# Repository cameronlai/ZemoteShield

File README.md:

# ZemoteShield
Zemote Shield for Zemote Universal Remote Control (on Arduino Uno and Nano)

This project, and all of its design files (including the layout), is licensed under the Creative Commons Attribution-ShareAlike 3.0 Unported license.

Related pages
- Project page: http://cameronlai.com/zemote/
- Zemote Firmware: https://github.com/cameronlai/ZemoteFirmware
- Zemote Host: https://github.com/cameronlai/ZemoteHost

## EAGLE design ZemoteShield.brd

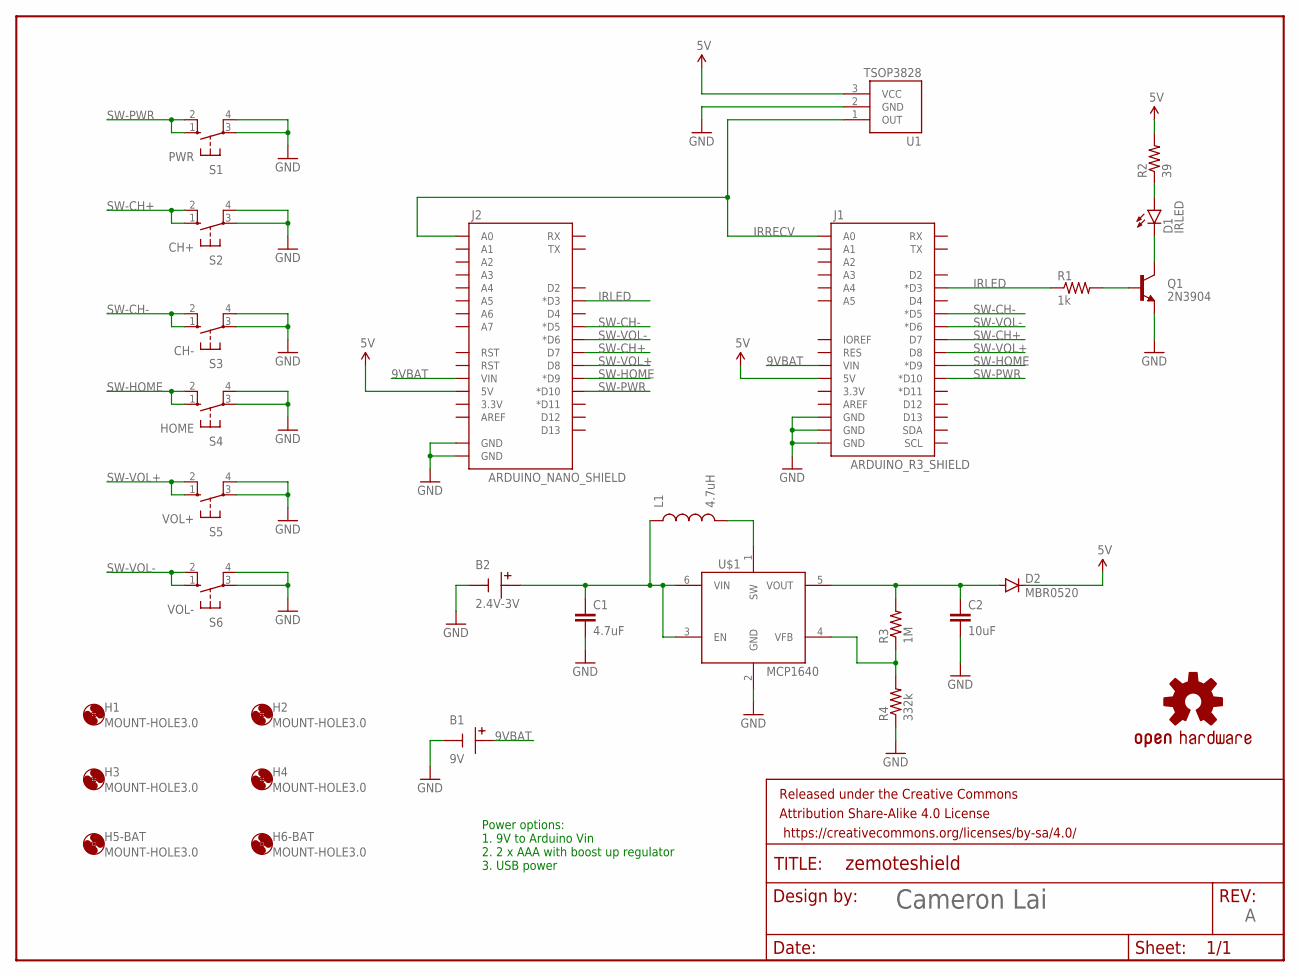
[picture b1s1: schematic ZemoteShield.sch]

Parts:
B1: 9V; BATTERY-2PIN-CON
B2: 2.4V-3V; BATTERY-2PIN-CON
C1: 4.7uF; 0603-CAP
C2: 10uF; 0805
D1: IRLED; LED5MM
D2: MBR0520; SOD-123
FRAME1: ZemoteShield; DUMMY
H1, H2, H3, H4, H5-BAT, H6-BAT: MOUNT-HOLE3.0; 3,0
J1: ARDUINO_R3_SHIELD; UNO_R3_SHIELD
J2: ARDUINO_NANO_SHIELD; NANO_SHIELD
L1: 4.7uH; 1210
LOGO1: OSHW-LOGOL; OSHW-LOGO-L
Q1: 2N3904; TO-92
R1: 1k; AXIAL-0.4
R2: 39; AXIAL-0.6
R3: 1M; 0603-RES
R4: 332k; 0603-RES
S1: PWR; B3F-10XX
S2: CH+; B3F-10XX
S3: CH-; B3F-10XX
S4: HOME; B3F-10XX
S5: VOL+; B3F-10XX
S6: VOL-; B3F-10XX
U1: TSOP3828; BRM-2508
U$1: MCP1640; SOT23-6

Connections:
5V: D2.C, J1.5V, J2.5V, R2.P$2 (2), U1.3 (VCC)
9VBAT: B1.POS, J1.VIN, J2.VIN
AAABAT: B2.POS, C1.1, L1.1, U$1.3 (EN), U$1.6 (VIN)
GND: B1.NEG, B2.NEG, C1.2, C2.2, J1.GND@0 (GND), J1.GND@1 (GND), J1.GND@2 (GND), J2.GND@0 (GND), J2.GND@1 (GND), Q1.1 (E), R4.1, S1.3, S1.4 (P1), S2.3, S2.4 (P1), S3.3, S3.4 (P1), S4.3, S4.4 (P1), S5.3, S5.4 (P1), S6.3, S6.4 (P1), U1.2 (GND), U$1.2 (GND)
IRLED: J1.D3 (*D3), J2.D3 (*D3), R1.P$1 (1)
IRRECV: J1.A0, J2.A0, U1.1 (OUT)
unnamed: D1.K (C), Q1.3 (C)
unnamed: Q1.2 (B), R1.P$2 (2)
unnamed: D1.A, R2.P$1 (1)
unnamed: L1.2, U$1.1 (SW)
unnamed: C2.1, D2.A, R3.2, U$1.5 (VOUT)
unnamed: R3.1, R4.2, U$1.4 (VFB)
SW-CH+: J1.D7, J2.D7, S2.1 (S), S2.2 (S1)
SW-CH-: J1.D5 (*D5), J2.D5 (*D5), S3.1 (S), S3.2 (S1)
SW-HOME: J1.D9 (*D9), J2.D9 (*D9), S4.1 (S), S4.2 (S1)
SW-PWR: J1.D10 (*D10), J2.D10 (*D10), S1.1 (S), S1.2 (S1)
SW-VOL+: J1.D8, J2.D8, S5.1 (S), S5.2 (S1)
SW-VOL-: J1.D6 (*D6), J2.D6 (*D6), S6.1 (S), S6.2 (S1)

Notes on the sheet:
Power options: 1. 9V to Arduino Vin 2. 2 x AAA with boost up regulator 3. USB power

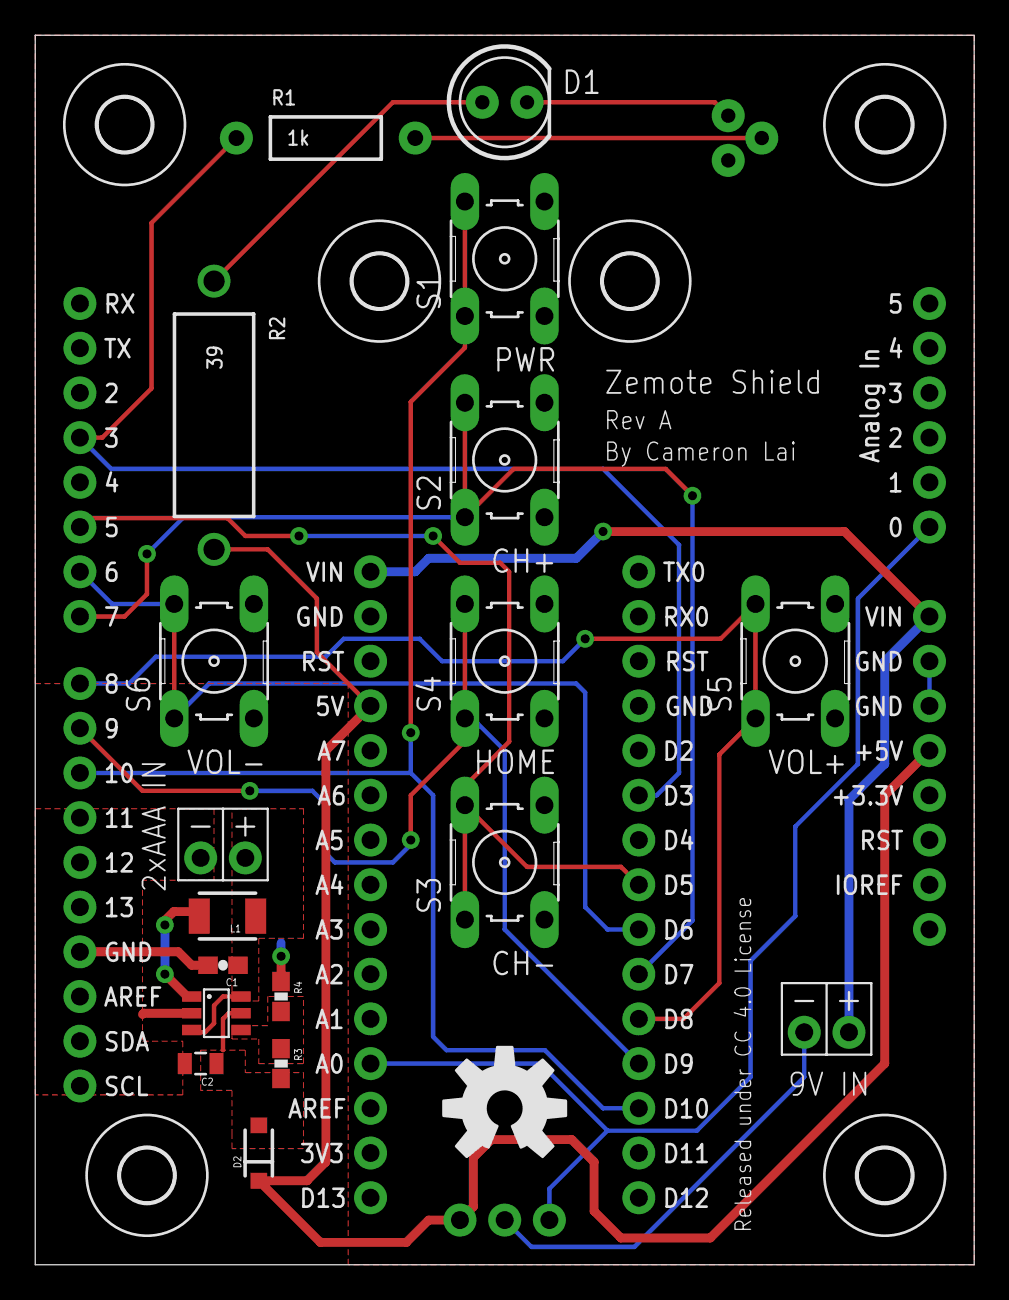
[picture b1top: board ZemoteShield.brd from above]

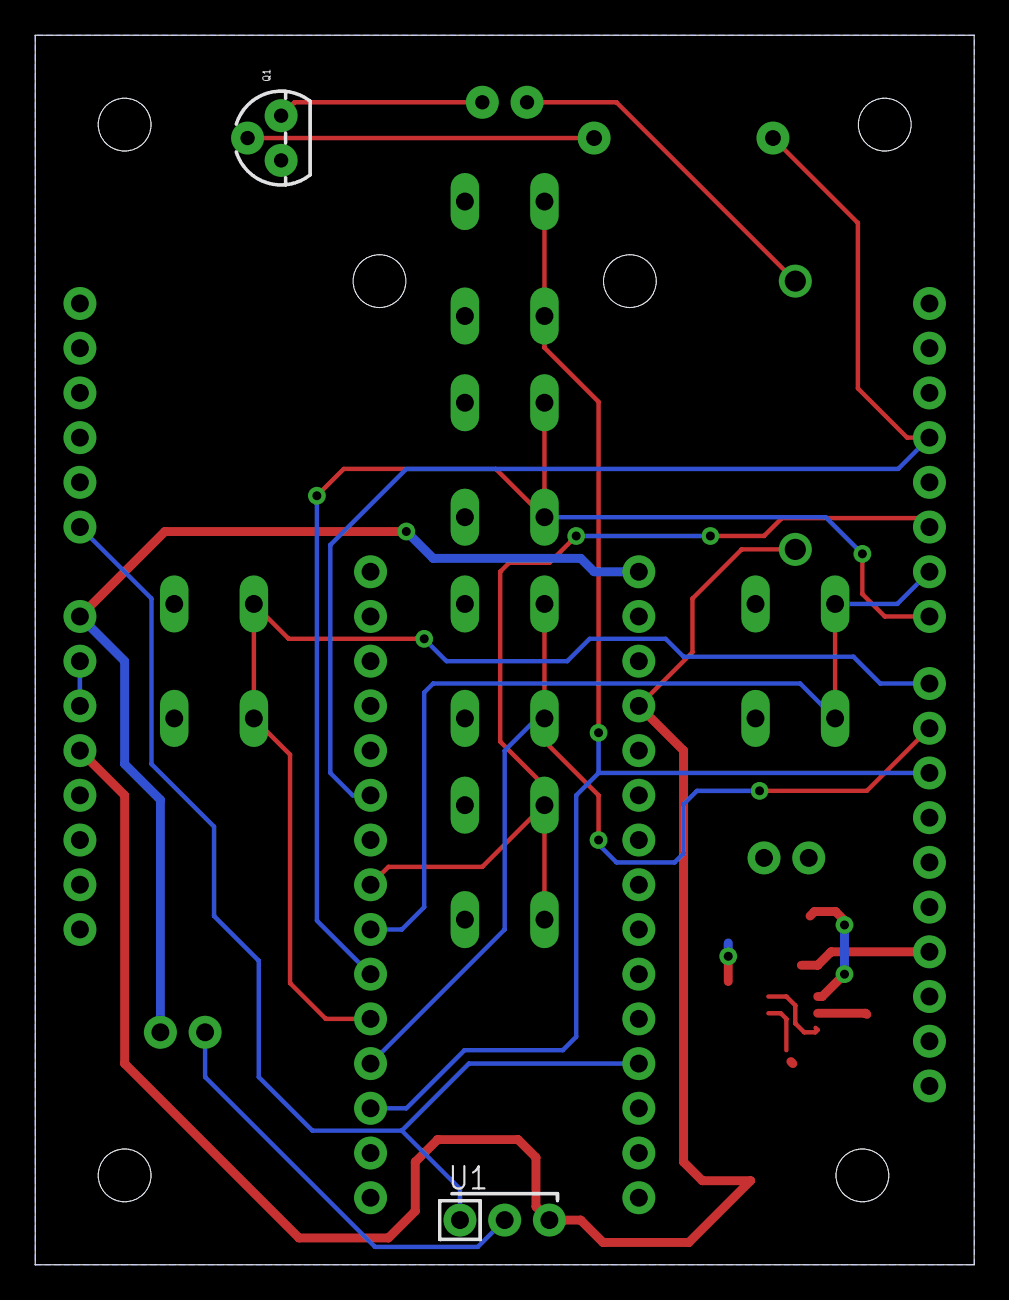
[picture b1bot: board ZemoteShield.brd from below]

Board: 2 copper layers, 53.3 x 69.8 mm, 30 parts (2 on the bottom side), 18 nets.

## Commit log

2015-07-18 Add .sch and .brd file
2015-07-18 Update README.md
    First commit

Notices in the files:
ZemoteShield.brd:
Released under CC 4.0 License
parts and their libraries:
SparkFun-Aesthetics: Licensing: Creative Commons ShareAlike 4.0 International - https://creativecommons.org/licenses/by-sa/4.0
SparkFun-Aesthetics: Released under the Creative Commons Attribution Share-Alike 4.0 License
SparkFun-Aesthetics: https://creativecommons.org/licenses/by-sa/4.0
